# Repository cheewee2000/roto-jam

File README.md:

roto-jam
========

Roto Jam Machine for thin shell casting in jamming molds

http://cwandt.com/#roto-jam

BOM at
http://bit.ly/rotojam-bom

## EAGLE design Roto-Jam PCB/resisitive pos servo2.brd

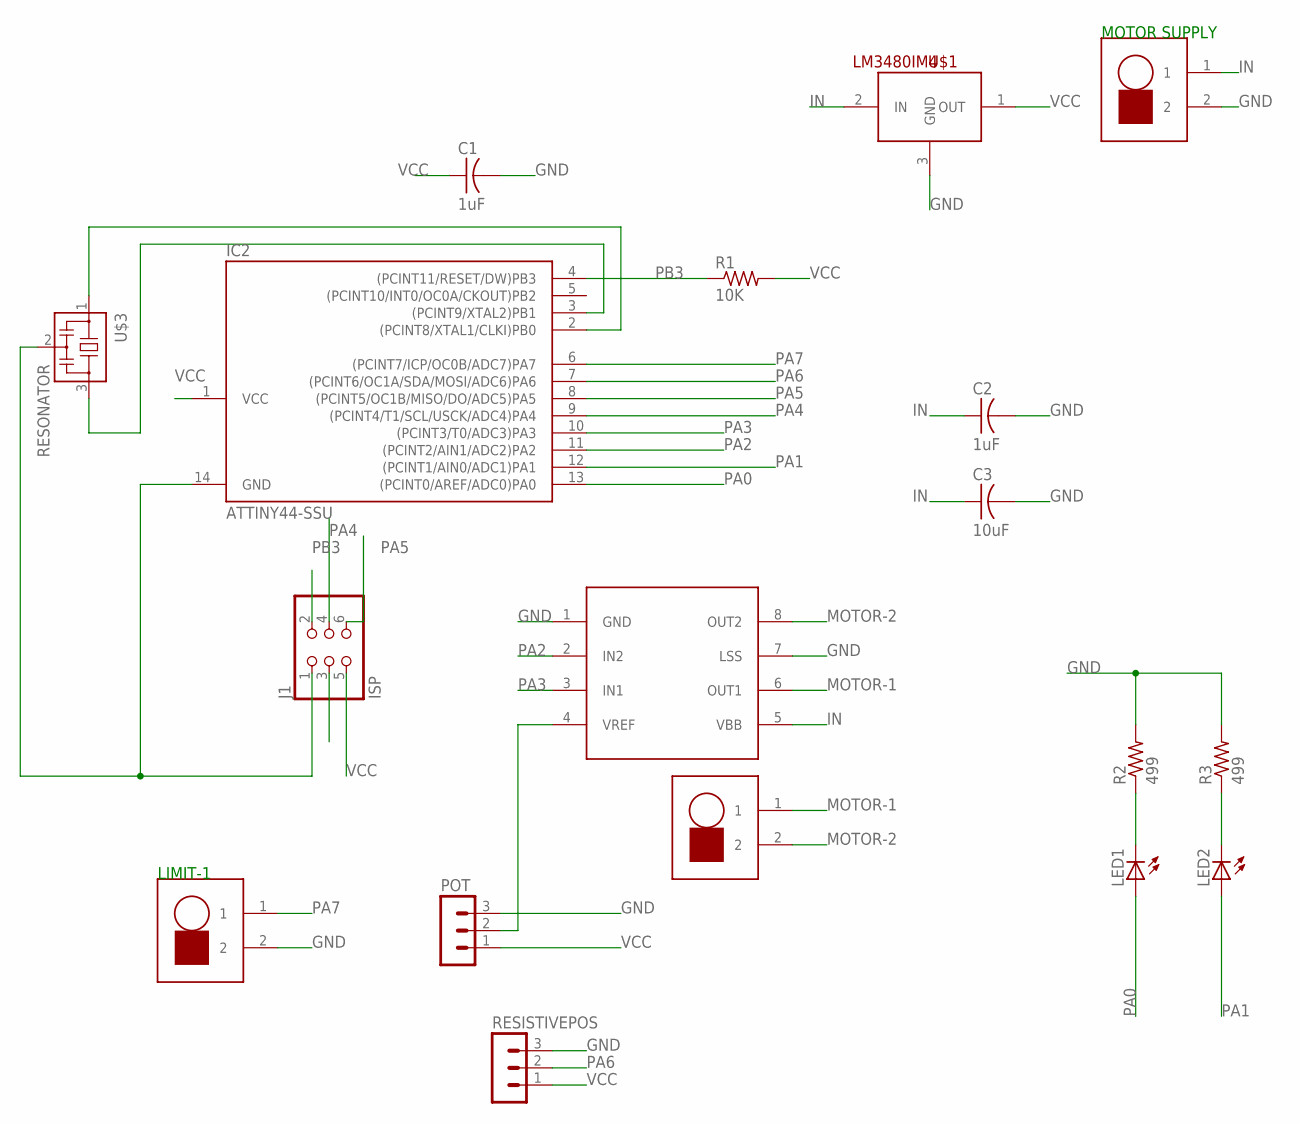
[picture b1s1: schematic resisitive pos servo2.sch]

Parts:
C1, C2: 1uF; C1206
C3: 10uF; C1206
IC2: ATTINY44-SSU; SOIC14
J1: ISP; 2X03SMD
LED1, LED2: LEDSMT1206; 1206
MOTOR-SUPPLY: 3.5MMSCREWTERMINAL2; SCREWTERMINAL-3.5MM-2-NS
POT: MA03-1
R1: 10K; R1206FAB
R2, R3: 499; R1206FAB
RESISTIVEPOS: MA03-1
U$1: LM3480IM4; SOT23-3
U$2, U$5: 3.5MMSCREWTERMINAL2; SCREWTERMINAL-3.5MM-2-NS
U$3: RESONATOR; EFOBM
U$6: A4953-H-BRIDGE-MOTOR-DRIVER; SOIC8

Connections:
GND: C1.2, C2.2, C3.2, IC2.14 (GND), J1.1, MOTOR-SUPPLY.2, POT.3, R2.2, R3.2, RESISTIVEPOS.3, U$1.3 (GND), U$3.2, U$5.2, U$6.1 (GND), U$6.7 (LSS)
IN: C2.1, C3.1, MOTOR-SUPPLY.1, U$1.2 (IN), U$6.5 (VBB)
MOTOR-1: U$2.1, U$6.6 (OUT1)
MOTOR-2: U$2.2, U$6.8 (OUT2)
unnamed: LED1.C, R2.1
unnamed: IC2.3 ((PCINT9/XTAL2)PB1), U$3.3
unnamed: IC2.2 ((PCINT8/XTAL1/CLKI)PB0), U$3.1
unnamed: LED2.C, R3.1
unnamed: POT.2, U$6.4 (VREF)
PA0: IC2.13 ((PCINT0/AREF/ADC0)PA0), LED1.A
PA1: IC2.12 ((PCINT1/AIN0/ADC1)PA1), LED2.A
PA2: IC2.11 ((PCINT2/AIN1/ADC2)PA2), U$6.2 (IN2)
PA3: IC2.10 ((PCINT3/T0/ADC3)PA3), U$6.3 (IN1)
PA4: IC2.9 ((PCINT4/T1/SCL/USCK/ADC4)PA4), J1.4
PA5: IC2.8 ((PCINT5/OC1B/MISO/DO/ADC5)PA5), J1.6
PA6: IC2.7 ((PCINT6/OC1A/SDA/MOSI/ADC6)PA6), J1.3, RESISTIVEPOS.2
PA7: IC2.6 ((PCINT7/ICP/OC0B/ADC7)PA7), U$5.1
PB3: IC2.4 ((PCINT11/RESET/DW)PB3), J1.2, R1.1
VCC: C1.1, IC2.1 (VCC), J1.5, POT.1, R1.2, RESISTIVEPOS.1, U$1.1 (OUT)

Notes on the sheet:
MOTOR SUPPLY
LIMIT-1

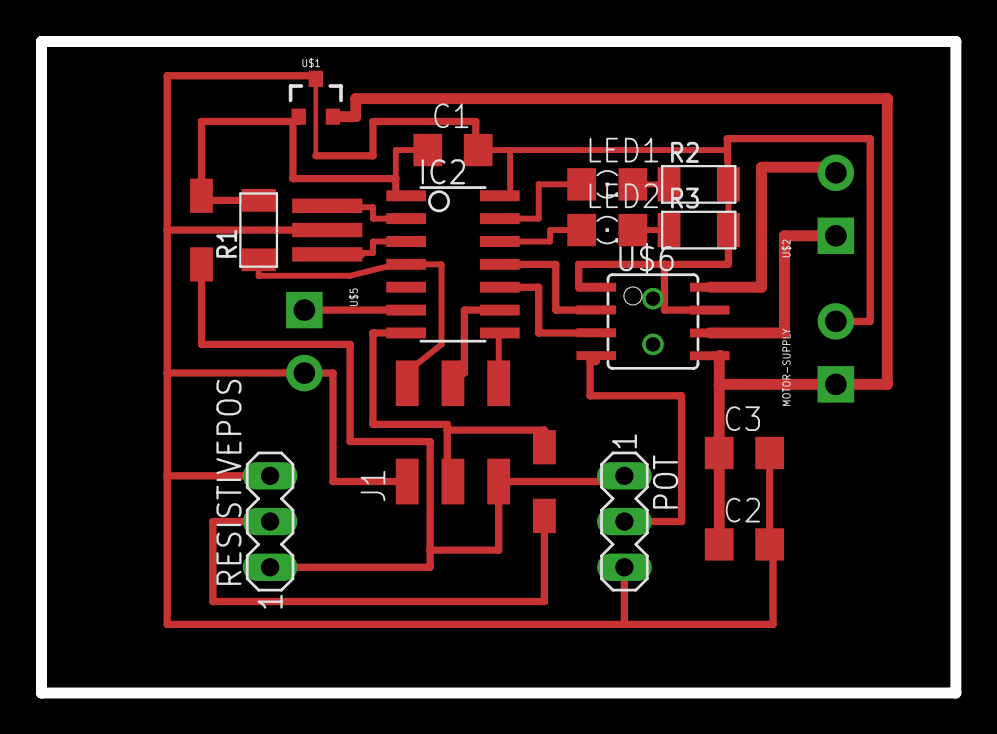
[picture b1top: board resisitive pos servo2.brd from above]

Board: 2 copper layers, 50.8 x 36.2 mm, 18 parts (0 on the bottom side), 19 nets.

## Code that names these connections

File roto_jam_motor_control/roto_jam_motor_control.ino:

const int analogInPin = 6;  // Analog input pin that the potentiometer is attached to

const int motor1Pin = 2;    //PA2
const int motor2Pin = 3;    //PA3
const int ledPin1 = 0;    //PA0
const int ledPin2 = 1;    //PA1

const int switchPin = 7;    // PA7
boolean switchPressed=false;

unsigned int recording[15];

unsigned int recCount=0;
unsigned long lastMillis=0;
unsigned int sampleTime=1000;

float motorSpeed=.5;

void setup()  
{
  digitalWrite(analogInPin, LOW);

  pinMode(motor1Pin, OUTPUT); 
  pinMode(motor2Pin, OUTPUT); 
  pinMode(ledPin1, OUTPUT);
  pinMode(ledPin2, OUTPUT);

  digitalWrite(switchPin, HIGH);

  for (int i=0; i < (sizeof(recording)/sizeof(int))-1; i++){
    recording[i]=-1;
  }
}

void loop()
{
  if(digitalRead(switchPin)==LOW) {   // button hold down
    record(); 
  }
  else{
    if(switchPressed){
      switchPressed=false; 
      recCount=0;
    }
    play();
  }
}


void record(){

  if(millis()-lastMillis>sampleTime){
    if(recCount>(sizeof(recording)/sizeof(int))-1){
      recCount=0;  
    }

    recording[recCount]=analogRead(analogInPin);
    recCount++;
    lastMillis=millis();

    //flash lights
    digitalWrite(ledPin1, recCount%2);  
    digitalWrite(ledPin2, (recCount+1)%2);  

  }


}


void play(){

  if(recCount>(sizeof(recording)/sizeof(int))-1){
    recCount=0;  
  }
  int pos=recording[recCount];

  if(pos>0){
    spinMotor(pos,true,motorSpeed);
  }

  else{
    runMotor(0,true,0);
    recCount++; 
  }

  if(millis()-lastMillis>sampleTime){
    recCount++;
    lastMillis=millis();


  }
}

void spinMotor(int targetPosition, boolean lightsOn, float sp){
  int currentPosition = analogRead(analogInPin);

  if(currentPosition<targetPosition){
    runMotor(1,lightsOn,sp);
  }

  else if(currentPosition>targetPosition){
    runMotor(-1,lightsOn,sp);
  }



  /*
  int currentPosition = analogRead(analogInPin);
   
   if (currentPosition<targetPosition) {
   int a=1023-targetPosition+currentPosition;
   int b=targetPosition-currentPosition;
   
   if(a<=b+100){
   //clockwise
   runMotor(1,lightsOn,sp);
   }
   else{
   //counterclockwise
   runMotor(-1,lightsOn,sp);
   }
   }
   else if (currentPosition>targetPosition){
   int a=1023-currentPosition+targetPosition;
   int b=currentPosition-targetPosition;
   if(a<=b){
   //counterclockwise
   runMotor(-1,lightsOn,sp); 
   }
   else{
   //clockwise
   runMotor(1,lightsOn,sp);
   }
   } 
   */
}


void runMotor(int c, boolean lightsOn, float sp){
  if(c==1){
    //clockwise
    digitalWrite(motor1Pin, HIGH);   // set leg 1 of the H-bridge low
    digitalWrite(motor2Pin, LOW);  // set leg 2 of the H-bridge high
    if(lightsOn){
      digitalWrite(ledPin1, HIGH);  
      digitalWrite(ledPin2, LOW);  
    }

  }
  else if(c==-1){
    //counterclockwise
    digitalWrite(motor1Pin, LOW);   // set leg 1 of the H-bridge lowa
    digitalWrite(motor2Pin, HIGH);  // set leg 2 of the H-bridge high
    if(lightsOn){
      digitalWrite(ledPin1, LOW);  
      digitalWrite(ledPin2, HIGH);  
    }
  }
  //rest
  else{
    digitalWrite(motor1Pin, LOW);   // set leg 1 of the H-bridge low
    digitalWrite(motor2Pin, LOW);  // set leg 2 of the H-bridge high
    if(lightsOn){
      digitalWrite(ledPin1, LOW);  
      digitalWrite(ledPin2, LOW);
    }
  }

  if(c!=0){
    //fake speed control
    delayMicroseconds(sp*10000.0);
    digitalWrite(motor1Pin, LOW); 
    digitalWrite(motor2Pin, LOW);
    if(lightsOn)digitalWrite(ledPin1, LOW);  
    if(lightsOn)digitalWrite(ledPin2, LOW); 
    delayMicroseconds(11000.0-sp*10000.0);
  }
}

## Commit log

2013-12-20 init
2013-12-20 merge

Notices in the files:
parts and their libraries:
SparkFun-PowerIC: Licensing: CC v3.0 Share-Alike You are welcome to use this library for commercial purposes.
